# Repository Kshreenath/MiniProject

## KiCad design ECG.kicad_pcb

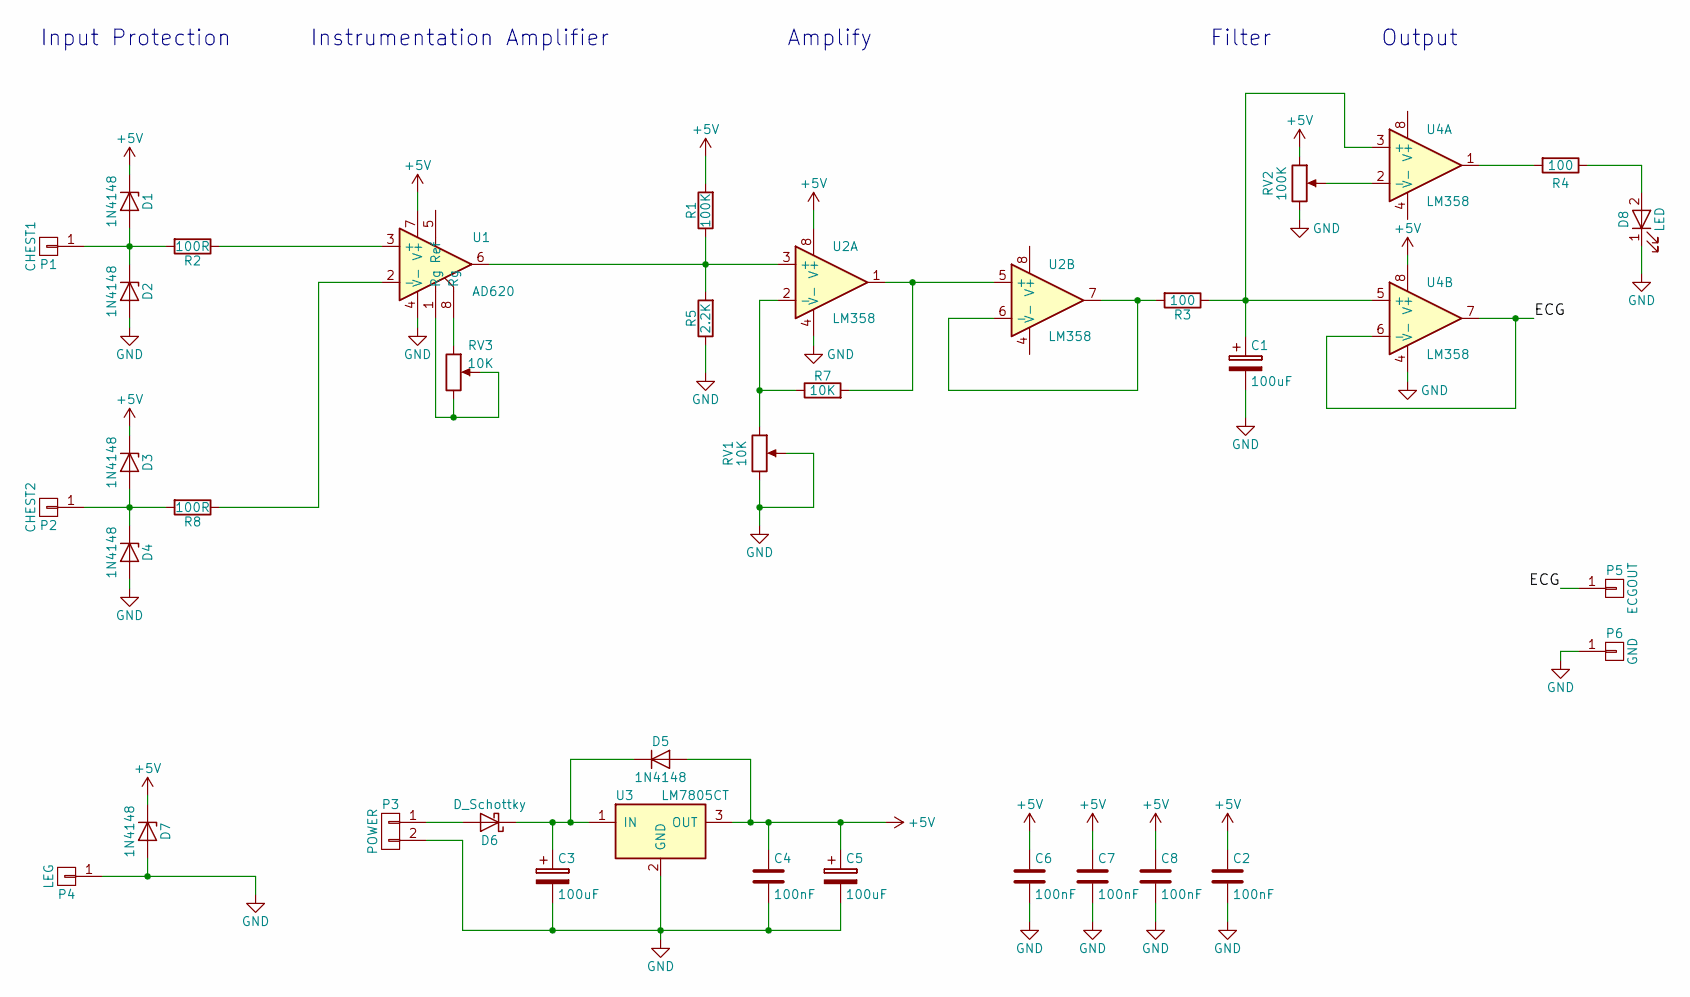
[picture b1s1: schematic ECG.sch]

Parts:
C1: 100uF; CP_Radial_D8.0mm_P3.50mm
C2, C4, C6, C7, C8: 100nF; C_Disc_D4.3mm_W1.9mm_P5.00mm
C3, C5: 100uF; CP_Radial_D6.3mm_P2.50mm
D1, D2, D3, D4, D5, D7: 1N4148; D_5W_P5.08mm_Vertical_KathodeUp
D6: D_Schottky; D_5W_P5.08mm_Vertical_KathodeUp
D8: LED; LED_D3.0mm
P1: CHEST1; SolderWirePad_single_1mmDrill
P2: CHEST2; SolderWirePad_single_1mmDrill
P3: POWER; Socket_Strip_Straight_1x02_Pitch2.54mm
P4: LEG; SolderWirePad_single_1mmDrill
P5: ECGOUT; SolderWirePad_single_1mmDrill
P6: GND; SolderWirePad_single_1mmDrill
R1: 100K; R3-LARGE_PADS
R2, R8: 100R; R3-LARGE_PADS
R3, R4: 100; R3-LARGE_PADS
R5: 2.2K; R3-LARGE_PADS
R7: 10K; R3-LARGE_PADS
RV1, RV3: 10K; Potentiometer_Triwood_RM-065
RV2: 100K; Potentiometer_Alps_RK163_Single_Vertical
U1: AD620; DIP-8_W7.62mm_LongPads
U2, U4: LM358; DIP-8_W7.62mm_LongPads
U3: LM7805CT; TO-220_Vertical

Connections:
+5V: C2.1, C4.1, C5.1, C6.1, C7.1, C8.1, D1.1 (K), D3.1 (K), D5.2 (A), D7.1 (K), R1.2, RV2.1, U1.7 (V+), U2.8 (V+), U3.3 (OUT), U4.8 (V+)
/ECG: P5.1, U4.6 (-), U4.7
GND: C1.2, C2.2, C3.2, C4.2, C5.2, C6.2, C7.2, C8.2, D2.2 (A), D4.2 (A), D7.2 (A), D8.1 (K), P3.2, P4.1, P6.1, R5.1, RV1.2, RV1.3, RV2.3, U1.4 (V-), U2.4 (V-), U3.2 (GND), U4.4 (V-)
unnamed: C1.1, R3.1, U4.3 (+), U4.5 (+)
unnamed: C3.1, D5.1 (K), D6.1 (K), U3.1 (IN)
unnamed: D1.2 (A), D2.1 (K), P1.1, R2.2
unnamed: D3.2 (A), D4.1 (K), P2.1, R8.2
unnamed: D6.2 (A), P3.1
unnamed: D8.2 (A), R4.1
unnamed: R1.1, R5.2, U1.6, U2.3 (+)
unnamed: R2.1, U1.3 (+)
unnamed: R3.2, U2.6 (-), U2.7
unnamed: R4.2, U4.1
unnamed: R7.1, RV1.1, U2.2 (-)
unnamed: R7.2, U2.1, U2.5 (+)
unnamed: R8.1, U1.2 (-)
unnamed: RV2.2, U4.2 (-)
unnamed: RV3.1, U1.8 (Rg)
unnamed: RV3.2, RV3.3, U1.1 (Rg)

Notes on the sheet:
Instrumentation Amplifier
Input Protection
Amplify
Filter
Output

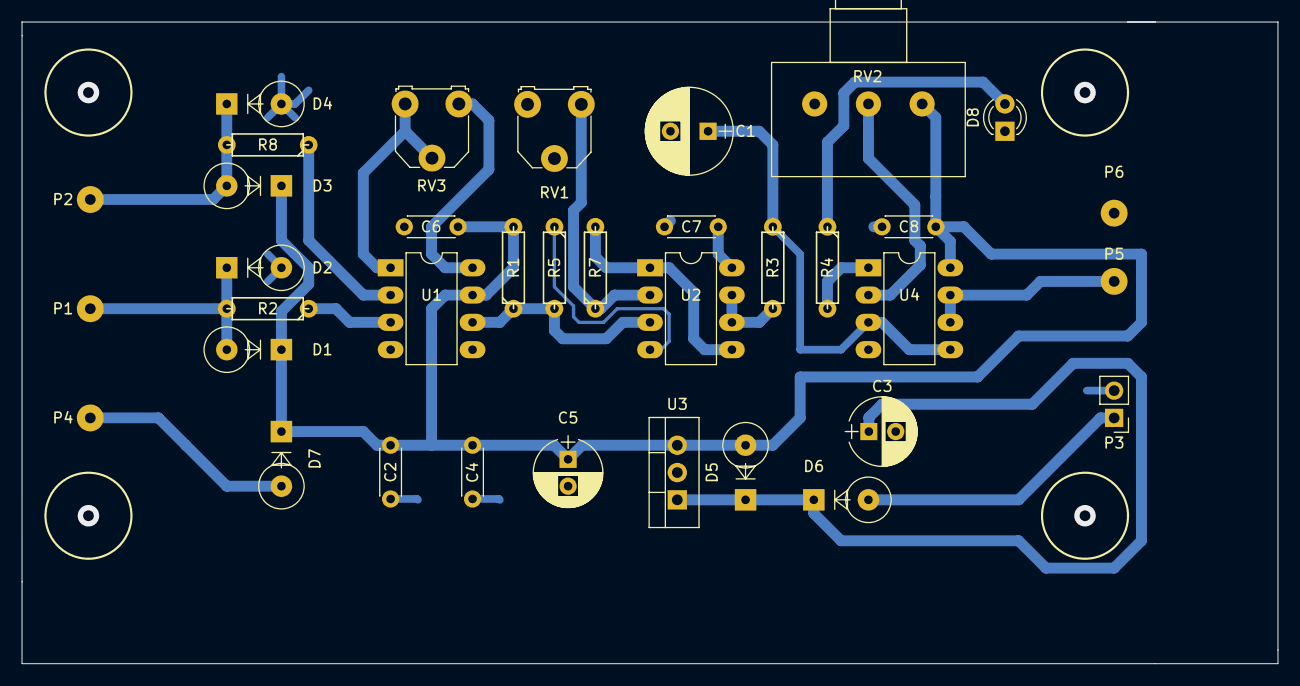
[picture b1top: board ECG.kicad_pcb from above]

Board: 2 copper layers, 116.8 x 59.7 mm, 36 parts (0 on the bottom side), 19 nets.

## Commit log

2020-04-28 Mini Project-1
